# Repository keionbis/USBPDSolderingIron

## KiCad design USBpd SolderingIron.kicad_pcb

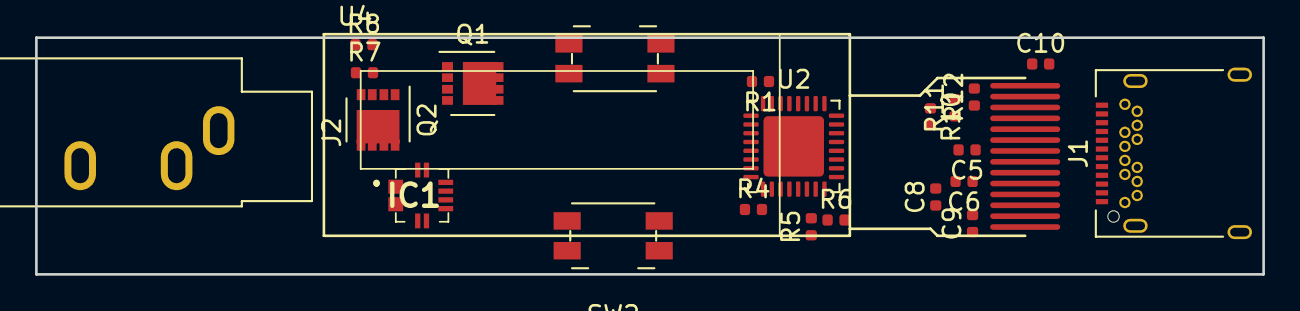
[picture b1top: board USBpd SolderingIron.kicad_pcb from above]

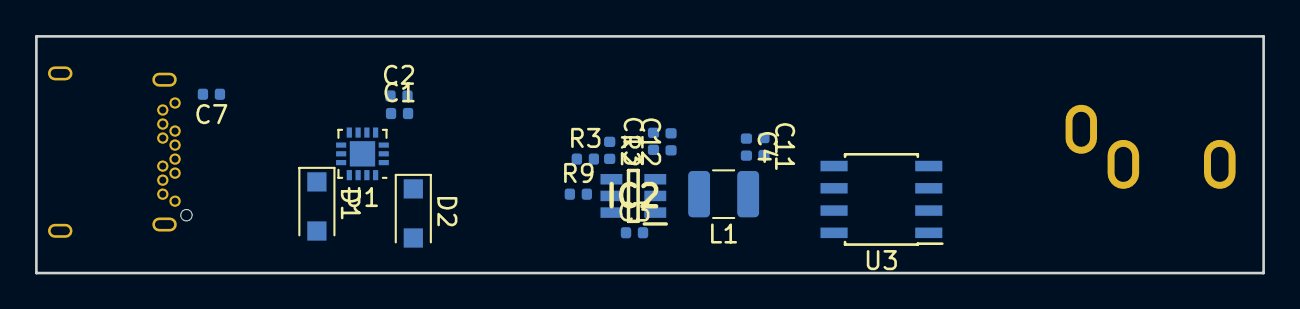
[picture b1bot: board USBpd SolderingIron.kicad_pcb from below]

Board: 2 copper layers, 70.0 x 13.5 mm, 40 parts (17 on the bottom side), 36 nets, no tracks yet.

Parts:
C1, C2, C3, C4, C5, C6, C7, C8, C9, C10, C11, C12, C13: C; C_0402_1005Metric
D1, D2: MM3Zxx; D_SOD-123F
IC1: ACS70331EESATR-005B3; ACS70331EESATR005B3
IC2: TPS562201DDCR; SOT95P280X110-6N
J1: USB_C_Receptacle; USB_C_Receptacle_Amphenol_12401548E4-2A
J2: AudioJack3_Ground; Jack_3.5mm_CUI_SJ1-3533NG_Horizontal
L1: L; L_1210_3225Metric
Q1: PSMN5R2-60YL; VSON-8_3.3x3.3mm_P0.65mm_NexFET
Q2: DMP3013SFV; VSON-8_3.3x3.3mm_P0.65mm_NexFET
R1, R2, R3, R4, R5, R6, R7, R8, R9, R10, R11, R12: R; R_0402_1005Metric
SW1, SW2: SW_Push; Panasonic_EVQPUJ_EVQPUA
U1: FUSB302BMPX; WQFN-14-1EP_2.5x2.5mm_P0.5mm_EP1.45x1.45mm
U2: STM32L432KBUx; QFN-32-1EP_5x5mm_P0.5mm_EP3.45x3.45mm
U3: MAX31855KASA; SOIC-8_3.9x4.9mm_P1.27mm
U4: SSD1306; SSD1306_OLED-0.91-128x32

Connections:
+3V3: C1.1, C2.1, C4.2, C5.1, C6.1, C11.2, IC1.12, L1.1, R3.1, R10.1, R11.2, U1.3, U1.4, U2.1, U2.5, U2.17, U3.4, U4.5, U4.8
BTN1: SW1.1, U2.13
BTN2: SW2.2, U2.6
CC1: D1.1, J1.A5, U1.10, U1.11
CC2: D2.1, J1.B5, U1.1, U1.14
CS: U2.10, U3.6
CURRSENSE: IC1.10, U2.7
D+: J1.A6, U2.22
D-: J1.B7, U2.21
GND: C1.2, C2.2, C3.2, C4.1, C5.2, C6.2, C7.2, C10.2, C11.1, C12.2, C13.2, D1.2, D2.2, IC1.5, IC2.1, J1.A1, J1.A12, J1.B1, J1.B12, J1.S1, J2.S, Q1.1, Q1.2, Q1.3, R1.2, R2.1, R4.1, R6.2, R12.2, SW1.2, SW2.1, U1.8, U1.9, U1.15, U2.16, U2.32, U2.33, U3.1, U3.2, U4.7
HEATER: IC1.3, IC1.4, J2.T
HEATERCONTROL: Q1.4, R4.2, U2.9
INT_N: U1.5, U2.8
MISO: U2.12, U3.7
NRES: U2.18, U4.9
unnamed: C3.1, IC2.6
unnamed: C7.1, U4.13
unnamed: C8.1, U4.3
unnamed: C8.2, U4.4
unnamed: C9.1, U4.1
unnamed: C9.2, U4.2
unnamed: C10.1, U4.14
unnamed: IC1.1, IC1.2, Q2.5
unnamed: IC2.2, L1.2
unnamed: IC2.4, R2.2, R3.2
unnamed: IC2.5, R9.2
unnamed: Q1.5, R8.2
unnamed: Q2.4, R7.1, R8.1
unnamed: R1.1, U2.31
unnamed: R12.1, U4.12
SCK: U2.11, U3.5
SCL: R10.2, U1.6, U2.19, U4.10
SDA: R11.1, U1.7, U2.20, U4.11
SENSOR: J2.R, U3.3
SUPPLYSENSE: R5.2, R6.1, U2.14
VBUS: C12.1, C13.1, IC2.3, J1.A4, J1.A9, J1.B4, J1.B9, Q2.1, Q2.2, Q2.3, R5.1, R7.2, R9.1, U1.2
